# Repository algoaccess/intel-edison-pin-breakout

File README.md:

# intel-edison-pin-breakout
Pin breakout of the Intel Edison Hirose connector to through-hole pin headers for prototyping.

##PCB Design software and addons used

1. Eagle 7.3.0: I use Standard but Light should still be able to open/modify the files.
2. Intel Edison library by [Sparkfun](https://github.com/sparkfun/Sparkfun_Blocks_Template) (in repo as Edison.lbr)

##Images

This has the 1.5mm Hirose connector which I hand soldered.

The smallest I can make this board to still allow the function of each pin to be silkscreened.

2-layer board so you can solder your pin headers on top or below the board.

##Schematic drawings
Images are exported from Eagle at 600dpi.

##Parts required

1) Hirose 70-pin DF40 Series Receptacle Connector. Such as the following taken from [Intel's website](http://www.intel.com/support/edison/sb/CS-035260.htm).

| Hirose part number        | Stacking height | Digi-key part number                   | Mouser part number   |
|---------------------------|-----------------|----------------------------------------|----------------------|
| DF40C-70DS-0.4V(51)       | 1.5 mm          | H11631TR-ND, [H11631CT-ND](http://www.digikey.sg/product-detail/en/DF40C-70DS-0.4V%2851%29/H11631CT-ND/1969510), H11631DKR-ND | 798-DF40C70DS04V51   |
| DF40C(2.0)-70DS-0.4V(51)  | 2.0 mm          | H11908TR-ND, H11908CT-ND, H11908DKR-ND | 798-DF40C2070DS04V51 |
| DF40HC(3.0)-70DS-0.4V(51) | 3.0 mm          | n/a                                    |                      |

I suggest the 1.5mm height header so the Intel Edison can be laid flat on the board without stressing the connectors between them.

2) 2x 35-pin through-hole pin-headers

I used a 36-pin header like [this](http://www.digikey.sg/product-detail/en/PBC36SAAN/S1011E-36-ND/859621) and broke away the last pin.

##PCB fabrication

PCB fabrication is currently done by [Seeedstudio](https://www.seeedstudio.com/service/index.php?r=pcb) based on the following settings. Remember to consult the [order submission guidelines](http://support.seeedstudio.com/knowledgebase/articles/422482-fusion-pcb-order-submission-guidelines) before submitting. Use the provided Gerber generator to produce the Gerber files.

Seeedstudio requires the following gerber files to be zipped up for submission:

1. Top Layer: pcbname.GTL
2. Top Solder Mask: pcbname.GTS
3. Top Silkscreen: pcbname.GTO
4. Bottom Layer: pcbname.GBL
5. Bottom Solder Mask﻿: pcbname.GBS
6. Bottom silkscreen: pcbname.GBO
7. Board Outline:pcbname.GML/GKO
8. Drills: pcbname.TXT
9. Inner Layer: pcbname.GL2(for 4 layer)
10. Inner Layer: pcbname.GL3(for 4 layer)

The zip file has been uploaded to the Releases section.

###My Fabrication Settings: 

1. Layer: 2
2. PCB Dimension: 10cm Max * 10cm Max
3. PCB Thickness: 1.6mm
4. PCB Qty: 10
5. PCB Color: Green
6. Surface Finish: ENIG (due to fine pitch of the pins)
7. Copper weight: 1oz
8. Panalized PCBs: 1
9. Expedited Option: No

##References
1. [Intel Edison Module Hardware guide](http://www.intel.com/support/edison/sb/CS-035274.htm)
2. [Sparkfun Intel Edison layout diagram](https://cdn.sparkfun.com/assets/learn_tutorials/3/2/2/edison-pinout.pdf)

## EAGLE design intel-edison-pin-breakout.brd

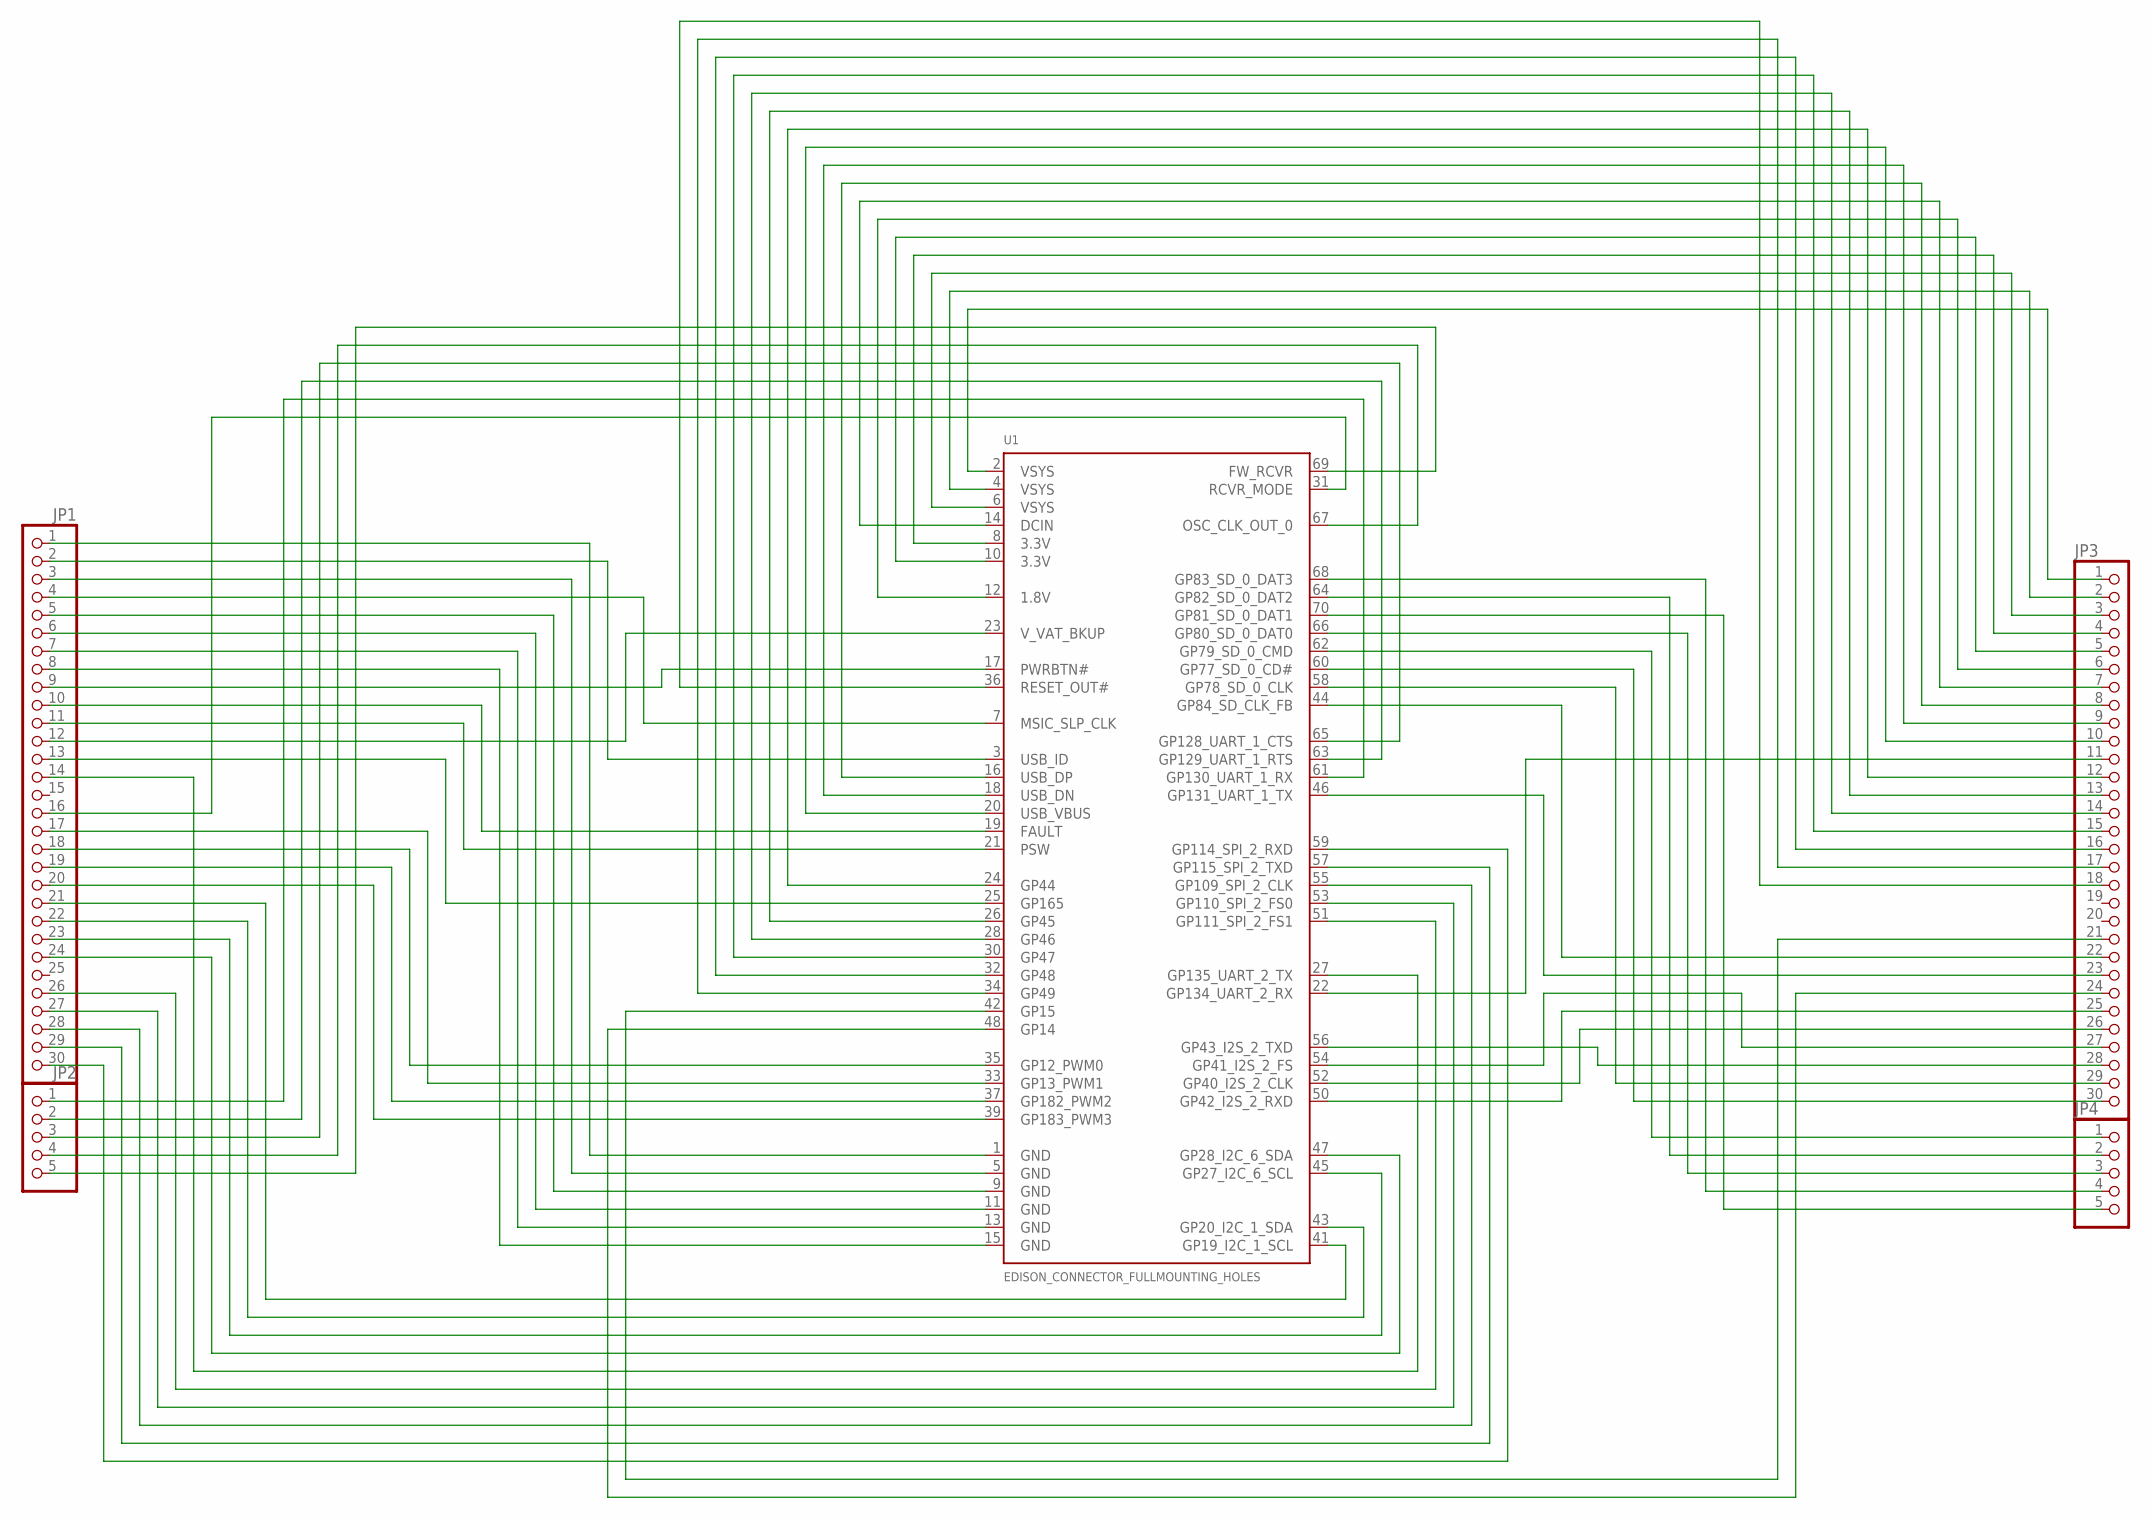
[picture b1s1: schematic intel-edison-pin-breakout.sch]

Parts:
JP1, JP3: PINHD-1X30; 1X30
JP2, JP4: PINHD-1X5; 1X05
U1: EDISON_CONNECTOR_FULLMOUNTING_HOLES; EDISON_DAUGHTER

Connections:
unnamed: JP1.1, U1.1 (GND)
unnamed: JP1.2, U1.3 (USB_ID)
unnamed: JP1.3, U1.5 (GND)
unnamed: JP1.4, U1.7 (MSIC_SLP_CLK)
unnamed: JP1.5, U1.9 (GND)
unnamed: JP1.6, U1.11 (GND)
unnamed: JP1.7, U1.13 (GND)
unnamed: JP1.8, U1.15 (GND)
unnamed: JP1.9, U1.17 (PWRBTN#)
unnamed: JP1.10, U1.19 (FAULT)
unnamed: JP1.11, U1.21 (PSW)
unnamed: JP1.12, U1.23 (V_VAT_BKUP)
unnamed: JP1.13, U1.25 (GP165)
unnamed: JP1.17, U1.33 (GP13_PWM1)
unnamed: JP1.16, U1.31 (RCVR_MODE)
unnamed: JP1.18, U1.35 (GP12_PWM0)
unnamed: JP1.19, U1.37 (GP182_PWM2)
unnamed: JP1.20, U1.39 (GP183_PWM3)
unnamed: JP1.21, U1.41 (GP19_I2C_1_SCL)
unnamed: JP1.22, U1.43 (GP20_I2C_1_SDA)
unnamed: JP1.23, U1.45 (GP27_I2C_6_SCL)
unnamed: JP1.24, U1.47 (GP28_I2C_6_SDA)
unnamed: JP1.26, U1.51 (GP111_SPI_2_FS1)
unnamed: JP1.27, U1.53 (GP110_SPI_2_FS0)
unnamed: JP1.28, U1.55 (GP109_SPI_2_CLK)
unnamed: JP1.29, U1.57 (GP115_SPI_2_TXD)
unnamed: JP1.30, U1.59 (GP114_SPI_2_RXD)
unnamed: JP1.14, U1.27 (GP135_UART_2_TX)
unnamed: JP2.1, U1.61 (GP130_UART_1_RX)
unnamed: JP2.2, U1.63 (GP129_UART_1_RTS)
unnamed: JP2.3, U1.65 (GP128_UART_1_CTS)
unnamed: JP2.4, U1.67 (OSC_CLK_OUT_0)
unnamed: JP2.5, U1.69 (FW_RCVR)
unnamed: JP3.1, U1.2 (VSYS)
unnamed: JP3.2, U1.4 (VSYS)
unnamed: JP3.3, U1.6 (VSYS)
unnamed: JP3.4, U1.8 (3.3V)
unnamed: JP3.5, U1.10 (3.3V)
unnamed: JP3.6, U1.12 (1.8V)
unnamed: JP3.7, U1.14 (DCIN)
unnamed: JP3.8, U1.16 (USB_DP)
unnamed: JP3.9, U1.18 (USB_DN)
unnamed: JP3.10, U1.20 (USB_VBUS)
unnamed: JP3.18, U1.36 (RESET_OUT#)
unnamed: JP3.12, U1.24 (GP44)
unnamed: JP3.13, U1.26 (GP45)
unnamed: JP3.14, U1.28 (GP46)
unnamed: JP3.15, U1.30 (GP47)
unnamed: JP3.16, U1.32 (GP48)
unnamed: JP3.17, U1.34 (GP49)
unnamed: JP3.11, U1.22 (GP134_UART_2_RX)
unnamed: JP3.21, U1.42 (GP15)
unnamed: JP4.5, U1.70 (GP81_SD_0_DAT1)
unnamed: JP4.4, U1.68 (GP83_SD_0_DAT3)
unnamed: JP3.24, U1.48 (GP14)
unnamed: JP4.3, U1.66 (GP80_SD_0_DAT0)
unnamed: JP4.2, U1.64 (GP82_SD_0_DAT2)
unnamed: JP4.1, U1.62 (GP79_SD_0_CMD)
unnamed: JP3.30, U1.60 (GP77_SD_0_CD#)
unnamed: JP3.29, U1.58 (GP78_SD_0_CLK)
unnamed: JP3.27, U1.54 (GP41_I2S_2_FS)
unnamed: JP3.23, U1.46 (GP131_UART_1_TX)
unnamed: JP3.26, U1.52 (GP40_I2S_2_CLK)
unnamed: JP3.25, U1.50 (GP42_I2S_2_RXD)
unnamed: JP3.22, U1.44 (GP84_SD_CLK_FB)
unnamed: JP3.28, U1.56 (GP43_I2S_2_TXD)

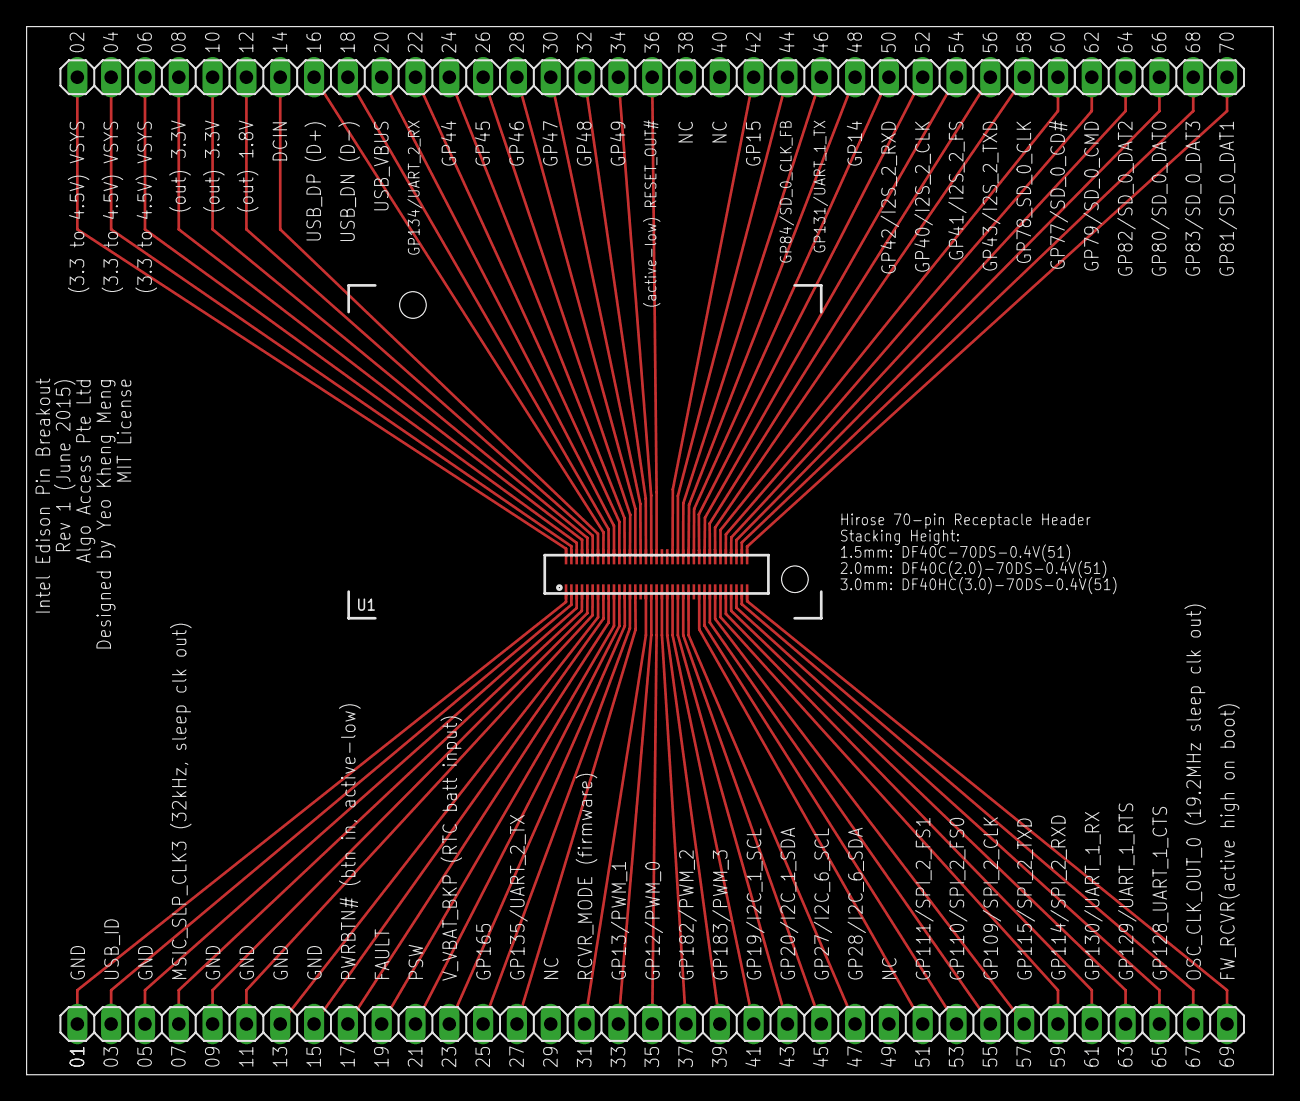
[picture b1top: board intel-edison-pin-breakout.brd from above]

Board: 2 copper layers, 93.7 x 78.7 mm, 5 parts (0 on the bottom side), 66 nets.

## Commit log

2015-06-03 board width
2015-06-03 reduce board size
2015-06-03 last 6 wires of each corner have edges
2015-06-03 don't bend the last wire so much
2015-06-03 wires
2015-06-03 put them closer
2015-06-03 all pins fit on smaller board
2015-06-03 pin numbering
2015-06-03 a few labels
2015-06-04 dummy labels
2015-06-04 labels in right orientation
2015-06-04 wire movements and some labels
2015-06-04 bottom labels
2015-06-04 pin names
2015-06-04 label changes
2015-06-04 mint license
2015-06-04 hirose connector label
2015-06-04 Seeed files
2015-06-04 images
2015-06-04 rotate board
2015-06-04 2 layers for PCB Fab
2015-07-08 actual images

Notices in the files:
intel-edison-pin-breakout.brd:
MIT License
